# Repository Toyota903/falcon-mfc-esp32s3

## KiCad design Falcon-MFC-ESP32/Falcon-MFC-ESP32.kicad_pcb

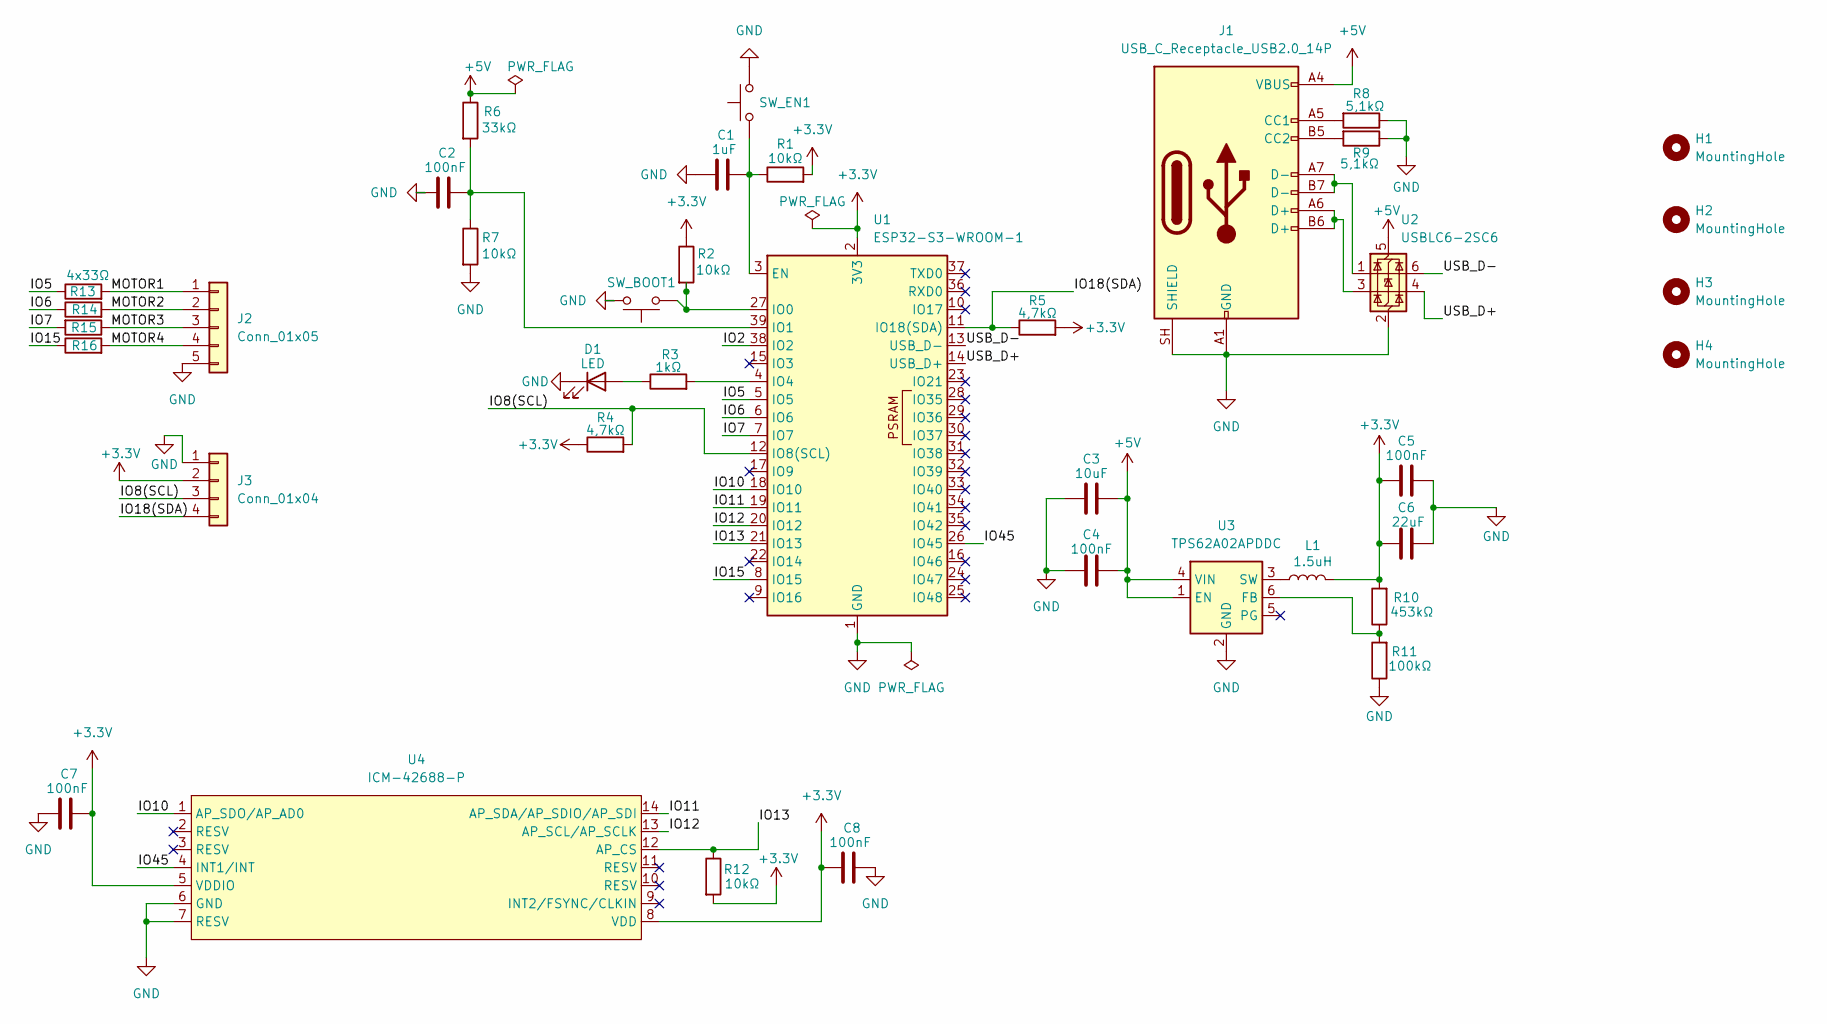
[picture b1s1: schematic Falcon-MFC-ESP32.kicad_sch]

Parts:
C1: 1uF; C_0603_1608Metric
C2, C4, C5, C7, C8: 100nF; C_0603_1608Metric
C3: 10uF; C_0603_1608Metric
C6: 22uF; C_0805_2012Metric
D1: LED; LED_0603_1608Metric
H1, H2, H3, H4: MountingHole; MountingHole_3.2mm_M3
J1: USB_C_Receptacle_USB2.0_14P; USB_C_Receptacle_HRO_TYPE-C-31-M-12
J2: Conn_01x05; PinHeader_1x05_P2.54mm_Vertical
J3: Conn_01x04; PinHeader_1x04_P2.54mm_Vertical
L1: 1.5uH; L_0805_2012Metric_Pad1.05x1.20mm_HandSolder
R1, R2, R7, R12: 10kΩ; R_0603_1608Metric_Pad0.98x0.95mm_HandSolder
R3: 1kΩ; R_0603_1608Metric_Pad0.98x0.95mm_HandSolder
R4, R5: 4,7kΩ; R_0603_1608Metric_Pad0.98x0.95mm_HandSolder
R6, R13, R15, R16: 33kΩ; R_0603_1608Metric_Pad0.98x0.95mm_HandSolder
R8, R9: 5,1kΩ; R_0603_1608Metric_Pad0.98x0.95mm_HandSolder
R10: 453kΩ; R_0603_1608Metric_Pad0.98x0.95mm_HandSolder
R11: 100kΩ; R_0603_1608Metric_Pad0.98x0.95mm_HandSolder
R14: 4x33Ω; R_0603_1608Metric_Pad0.98x0.95mm_HandSolder
SW_BOOT1: SW_SPST_B3U-1000P
SW_EN1: SW_SPST_B3U-1000P
U1: ESP32-S3-WROOM-1
U2: USBLC6-2SC6; SOT-23-6
U3: TPS62A02APDDC; SOT-23-6
U4: ICM-42688-P; LGA-14_3x2.5mm_P0.5mm_LayoutBorder3x4y; MPN ICM-42688-P; LCSC Part C1850418

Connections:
+3.3V: C5.2, C6.2, C7.2, C8.1, J3.2, L1.2, R1.2, R2.1, R4.1, R5.2, R10.2, R12.2, U1.2 (3V3), U4.5 (VDDIO), U4.8 (VDD)
+5V: C3.1, C4.1, J1.A4 (VBUS), J1.A9 (VBUS), J1.B4 (VBUS), J1.B9 (VBUS), R6.1, U2.5 (VBUS), U3.1 (EN), U3.4 (VIN)
/IO2: U1.38 (IO2)
/IO5: R13.1, U1.5 (IO5)
/IO6: R14.1, U1.6 (IO6)
/IO7: R16.2, U1.7 (IO7)
/IO8(SCL): J3.3, R4.2, U1.12 (IO8(SCL))
/IO10: U1.18 (IO10), U4.1 (AP_SDO/AP_AD0)
/IO11: U1.19 (IO11), U4.14 (AP_SDA/AP_SDIO/AP_SDI)
/IO12: U1.20 (IO12), U4.13 (AP_SCL/AP_SCLK)
/IO13: R12.1, U1.21 (IO13), U4.12 (AP_CS)
/IO15: R15.1, U1.8 (IO15)
/IO18(SDA): J3.4, R5.1, U1.11 (IO18(SDA))
/IO45: U1.26 (IO45), U4.4 (INT1/INT)
/MOTOR1: J2.1, R13.2
/MOTOR2: J2.2, R14.2
/MOTOR3: J2.3, R16.1
/MOTOR4: J2.4, R15.2
/USB_D+: U1.14 (USB_D+), U2.4 (I/O2)
/USB_D-: U1.13 (USB_D-), U2.6 (I/O1)
GND: C1.1, C2.1, C3.2, C4.2, C5.1, C6.1, C7.1, C8.2, D1.1 (K), J1.A1 (GND), J1.A12 (GND), J1.B1 (GND), J1.B12 (GND), J1.SH (SHIELD), J2.5, J3.1, R7.2, R8.1, R9.1, R11.1, SW_BOOT1.2, SW_EN1.2, U1.1 (GND), U1.40 (GND), U1.41 (GND), U2.2 (GND), U3.2 (GND), U4.6 (GND), U4.7 (RESV)
unnamed: D1.2 (A), R3.1
unnamed: J1.A5 (CC1), R8.2
unnamed: J1.B5 (CC2), R9.2
unnamed: J1.A6 (D+), J1.B6 (D+), U2.3 (I/O2)
unnamed: J1.A7 (D-), J1.B7 (D-), U2.1 (I/O1)
unnamed: C1.2, R1.1, SW_EN1.1, U1.3 (EN)
unnamed: R2.2, SW_BOOT1.1, U1.27 (IO0)
unnamed: C2.2, R6.2, R7.1, U1.39 (IO1)
unnamed: R3.2, U1.4 (IO4)
unnamed: R10.1, R11.2, U3.6 (FB)
unnamed: L1.1, U3.3 (SW)

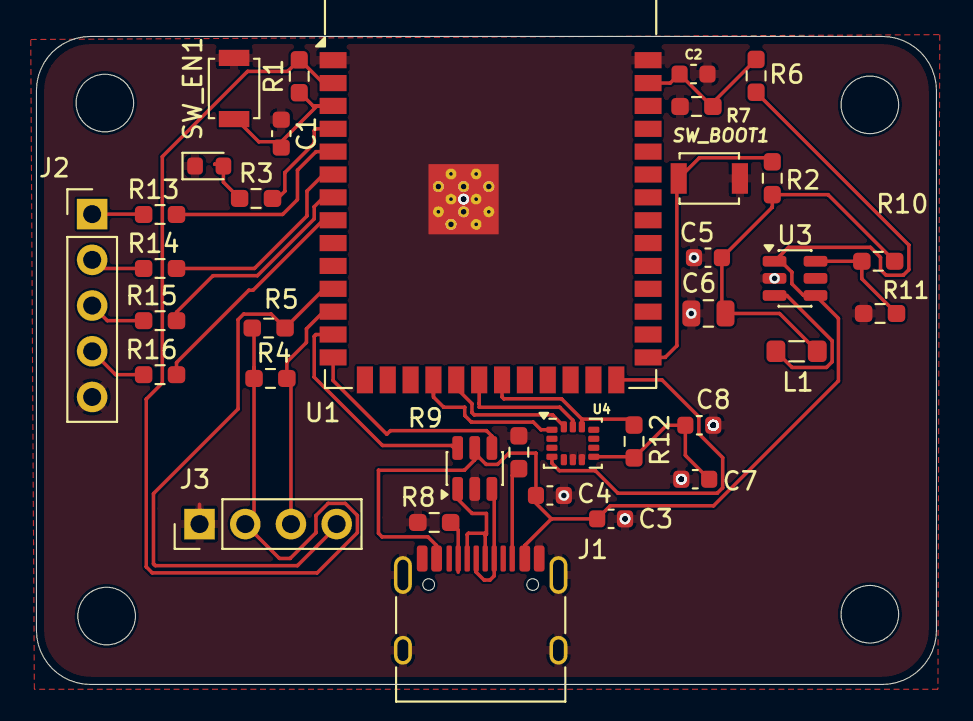
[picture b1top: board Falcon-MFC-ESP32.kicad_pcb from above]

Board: 2 copper layers, 50.0 x 36.0 mm, 39 parts (0 on the bottom side), 31 nets.
